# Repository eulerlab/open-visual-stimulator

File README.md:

## Open Visual Stimulator

This repository holds the resources for a flexible, spatial visual stimulator with up to 6 chromatic channels. It combines commercial digital light processing (DLP) devices with open hard- and software components that can be easily adapted to the experimentalist’s specific needs. With this we intend to start a community effort of sharing and further developing a common stimulator design.

Please find more details on the stimulator in the following publication:
  
_Franke K*, Maia Chagas A*, Zhao Z, Zimmermann MJY, Bartel P, Qiu Y, Szatko K, Baden T, Euler T# (2019). An arbitrary-spectrum spatial visual stimulator for vision research. eLife 2019;8:e48779, [10.7554/eLife.48779](https://elifesciences.org/articles/48779)._

For the newest changes and additions, see [release notes](https://github.com/eulerlab/open-visual-stimulator/blob/master/release_notes.md)

### Pictures

_Rendering of the 4-channel R-G-B-UV zebrafish stimulator (by MJY Zimmermann)._

_Rendering of through-the-conderser (TTC) G-UV mouse light stimulator (by MJY Zimmermann)._

_Rendering of through-the-objective (TTO) G-UV mouse light stimulator (by MJY Zimmermann)._ 

### Ordering of PCB boards

If you are interested in ordering boards and components, please find more information in the boards folder [readme](https://github.com/eulerlab/open-visual-stimulator/blob/master/boards/readme.md) file.

## Repository structure

```
├───pics                                      Pictures
├───boards                                    LED driver/blanking boards
│   ├───lcr_add-on                            - KiCad files for board that combines LCr and
|   |   |                                       blanking signals
|   |   ├───connector_coaxial.pretty          - BNC connector description (KiCad)
|   |   └───gerber                            - Gerber files for circuit board
│   ├───mosfet_circuit                        - KiCad files for board that switches switch LEDs
|   |   ├───connector_coaxial.pretty          - BNC connector description (KiCad)
|   |   └───gerber                            - Gerber files for circuit board
|   ├───mosfet_circuit_plus_voltage_regulator - KiCad files for board that combines voltage
|   |   |                                       regulator and LED switching
|   |   ├───connector_coaxial.pretty          - BNC connector description (KiCad)
|   |   └───gerbers                           - Gerber files for circuit board
|   ├───ssr_board                             - KiCad files for solid state relay board
|   |   └───gerbers                           - Gerber files for circuit board
|   └───arduino_code_for_testing_circuits     - Arduino code to emulate blanking and LCr signals
|       └───lcr_emulator
|
├───printed_parts                             OpenSCAD and STL files for 3D printed parts
|   |
│   ├───Fish_cinema                           - Fish tank used in the fish setup
│   ├───SSR_board                             - Designs for plate and cover of the SSR board
│   └───optical_components                    - optomechanical parts for LED assemblies
|           ├───fish_stimulator
|           ├───cmouse_stimulator
|           └───lcr_addons
├───calibration_mouse                         Calibration of dichroic mouse stimulator
│   ├───data                                  - recorded calibration data (custom LEDs and TFT monitor)
│   ├───datasheets                            - spectrometer data sheet, etc.
│   ├───filters                               - dichroic filter spectra
│   ├───light-sources                         - spectra of LEDs
│   ├───opsins                                - mouse opsin sensitivity curves
│   ├───scripts                               - Python scripts used in iPython notebooks
|   └───spectrometer-calibration-files        - USB2+ calibration data
|
└───calibration_zebrafish                     Calibration of tetrachromatic zebrafish stimulator
    ├───data                                  - recorded calibration data (custom LEDs)
    ├───datasheets                            - spectrometer & powermeter data sheet.
    ├───light-sources                         - LED spectra measured behind the teflon screen
    ├───opsins                                - zebrafish opsin sensitivity curves
    └───scripts                               - Python scripts used in iPython notebooks
```

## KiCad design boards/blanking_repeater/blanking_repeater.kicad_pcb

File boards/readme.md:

## LED driver/blanking boards

LED blanking circuits were inspired by earlier devices designed and built by R. Berndt (HIH Tübingen).

`lcr_add-on` - KiCad and Gerber files for the "logic board". This board combines the signals from the LCr with an external "blanking signal" to independently control up to three 3 LEDs per lightcrafter device. This board has a jumper option to disable the blanking signal altogether, which may be useful when e.g. using LCrs in MEA setups.

`mosfet_circuit` - KiCad and Gerber files for "LED driver board". This board uses the 5V logic signal from Lcr_addon ("logic board") to turn LEDs on and off. Users need to connect this board to an appropriate power suply (i.e. a power supply the is outputing the LED forward voltage).

`mosfet_circuit_plus_voltage_regulator` - KiCad and Gerber files for "LED driver board". This board uses the 5V logic signal from Lcr_addon ("logic board") to turn LEDs on and off. This board has a stepdown voltage regulator built-in. It is capable of 20V and 1.5A max output with the components present in its "1-click-bom.csv" file. (see "Components to populate the boards" for more details).

`ssr_board` - This board controls the LED power lines from the Lightcrafter by opening and closing them using solid state relays. The relays are controlled by a 5V signal (in this case the inverted blanking signal).

### General information about the printed circuit boards:

- For details on the design and function of the boards, see [preprint](https://www.biorxiv.org/content/10.1101/649566v1)).

- The boards were designed using [KiCad 5](http://www.kicad.org/) and can be ordered using the `Gerber.zip` file located in each board's `gerber` subfolder.

- Several "board on demand" companies are available, and the process of ordering is pretty much the same. A more detailed tutorial on how to do so can be found [here](https://www.youtube.com/watch?v=ENmDnoKs2hM) (for simply using the already available compressed files, go to minute 7 of the video).

- Companies providing "board on demand" service include:

   - [JLCPCB](https://jlcpcb.com/)
   - [PCBWAY](https://www.pcbway.com)
   - [OSH PARK](https://oshpark.com/)
   - [AISLER](https://aisler.net/)

### Components to populate the boards:

Components are listed on each board folder on a "comma separated value" file named `1-click-bom.csv`. Listed in the file are the quantity, identification and supplier of each component. They can also be ordered using [KitSpace](kitspace.org):

 - [LCr_addon on kitspace](https://kitspace.org/boards/github.com/eulerlab/open-visual-stimulator/boards/lcr_add-on/)
 - [mosfet circuit on kitspace](https://kitspace.org/boards/github.com/eulerlab/open-visual-stimulator/boards/mosfet_circuit/)
 - [mosfet  plus voltage regulator circuit on kitspace](https://kitspace.org/boards/github.com/eulerlab/open-visual-stimulator/boards/mosfet_circuit_plus_voltage_regulator/)

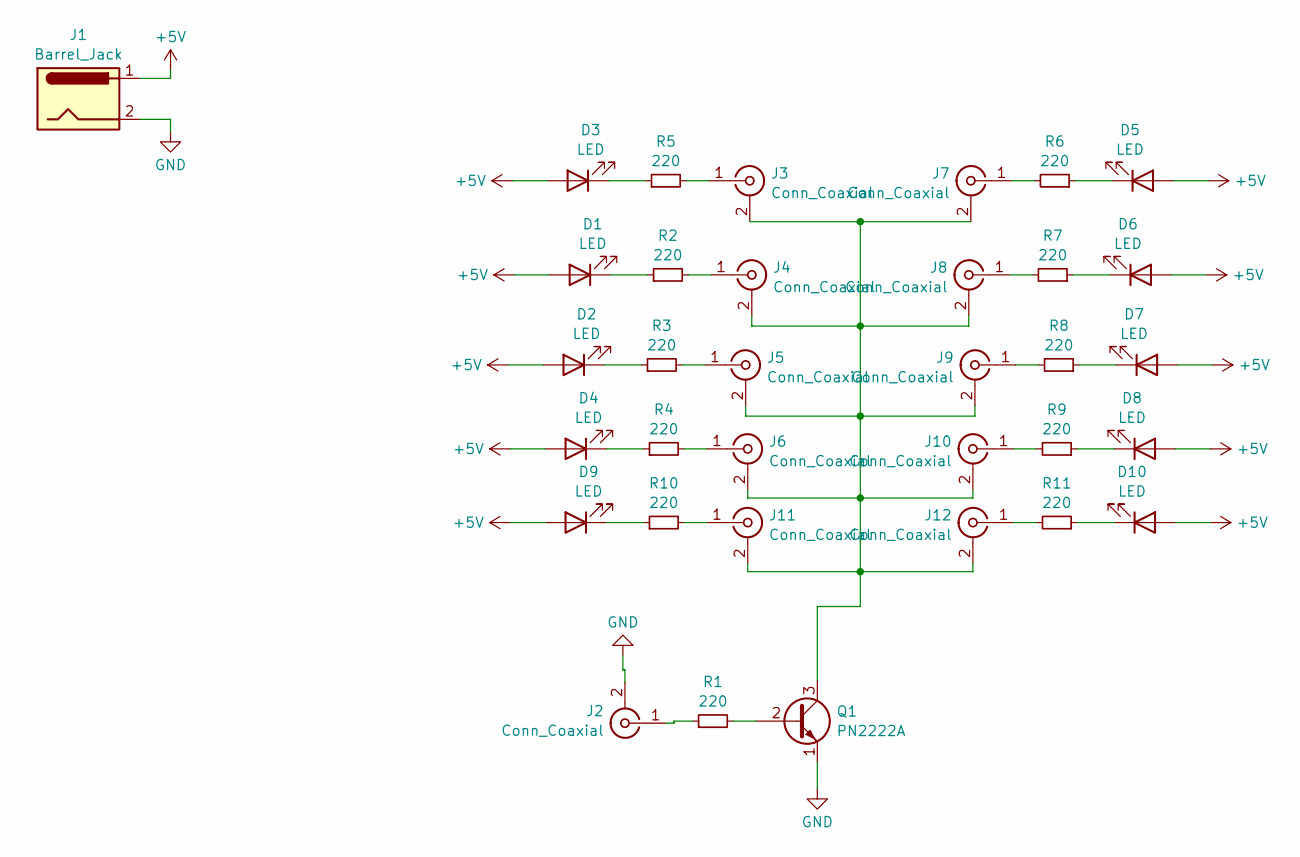
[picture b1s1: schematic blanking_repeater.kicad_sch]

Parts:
D1, D2, D3, D4, D5, D6, D7, D8, D9, D10: LED; LED_D3.0mm_Clear
J1: Barrel_Jack; BarrelJack_Horizontal
J2, J3, J4, J5, J6, J7, J8, J9, J10, J11, J12: Conn_Coaxial; BNC_Amphenol_B6252HB-NPP3G-50_Horizontal
Q1: PN2222A; TO-92_Inline
R1, R2, R3, R4, R5, R6, R7, R8, R9, R10, R11: 220; R_Axial_DIN0207_L6.3mm_D2.5mm_P10.16mm_Horizontal

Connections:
+5V: D1.2 (A), D2.2 (A), D3.2 (A), D4.2 (A), D5.2 (A), D6.2 (A), D7.2 (A), D8.2 (A), D9.2 (A), D10.2 (A), J1.1
GND: J1.2, J2.2 (Ext), Q1.1 (E)
unnamed: D1.1 (K), R2.1
unnamed: D2.1 (K), R3.1
unnamed: D3.1 (K), R5.1
unnamed: D4.1 (K), R4.1
unnamed: D5.1 (K), R6.1
unnamed: D6.1 (K), R7.1
unnamed: D7.1 (K), R8.1
unnamed: D8.1 (K), R9.1
unnamed: D9.1 (K), R10.1
unnamed: D10.1 (K), R11.1
unnamed: J2.1 (In), R1.1
unnamed: J3.1 (In), R5.2
unnamed: J4.1 (In), R2.2
unnamed: J5.1 (In), R3.2
unnamed: J6.1 (In), R4.2
unnamed: J7.1 (In), R6.2
unnamed: J8.1 (In), R7.2
unnamed: J9.1 (In), R8.2
unnamed: J3.2 (Ext), J4.2 (Ext), J5.2 (Ext), J6.2 (Ext), J7.2 (Ext), J8.2 (Ext), J9.2 (Ext), J10.2 (Ext), J11.2 (Ext), J12.2 (Ext), Q1.3 (C)
unnamed: J10.1 (In), R9.2
unnamed: J11.1 (In), R10.2
unnamed: J12.1 (In), R11.2
unnamed: Q1.2 (B), R1.2

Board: 2 copper layers, 34 parts (0 on the bottom side), 25 nets, no tracks yet.

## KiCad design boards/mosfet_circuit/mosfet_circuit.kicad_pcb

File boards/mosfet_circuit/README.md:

# Open Visual Stimulator - MOSFET Circuit PCB

A board ("LED driver board") for fast switching LEDs on/off, part of the Open Source visual stimulator project.

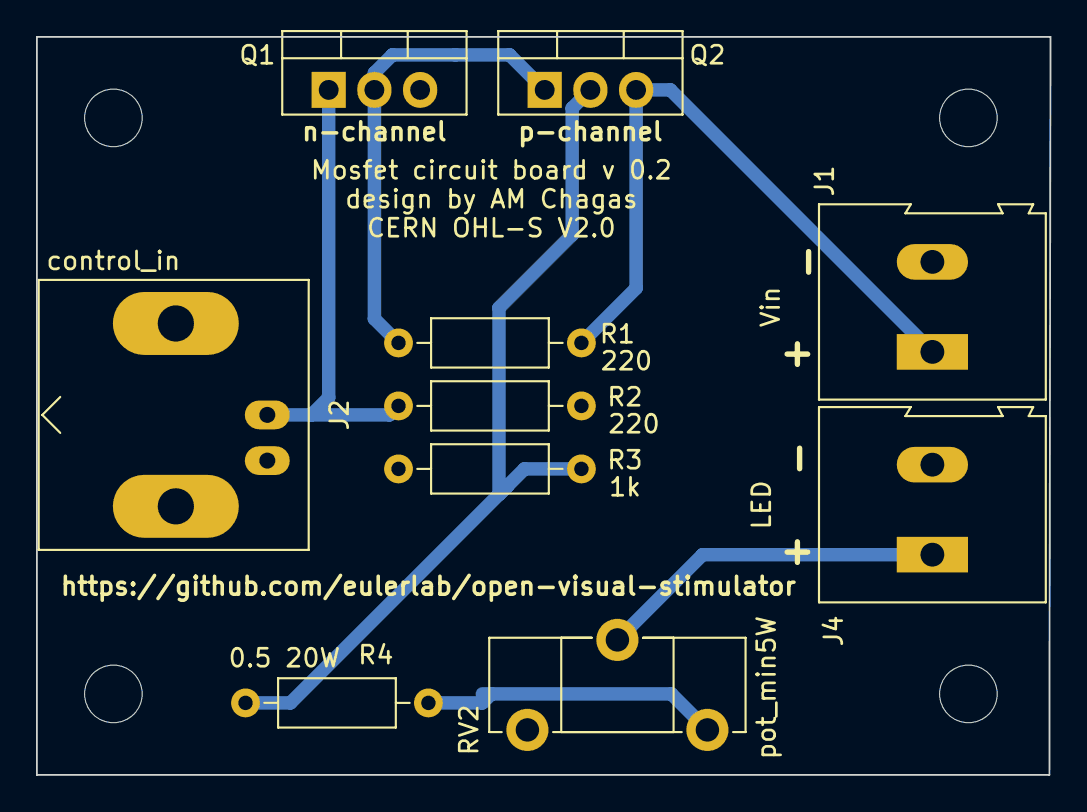
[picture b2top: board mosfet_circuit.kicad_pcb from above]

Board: 2 copper layers, 56.3 x 41.0 mm, 14 parts (0 on the bottom side), 7 nets.

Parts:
H1, H2, H3, H4: MountingHole; MountingHole_3.2mm_M3_DIN965
J1: Vin; TerminalBlock_Altech_AK300-2_P5.00mm
J2: control_in; BNC_Amphenol_B6252HB-NPP3G-50_Horizontal
J4: LED; TerminalBlock_Altech_AK300-2_P5.00mm
Q1: BUZ11; TO-220-3_Vertical
Q2: IRF4905; TO-220-3_Vertical
R1, R2: 220; R_Axial_DIN0207_L6.3mm_D2.5mm_P10.16mm_Horizontal
R3: 1k; R_Axial_DIN0207_L6.3mm_D2.5mm_P10.16mm_Horizontal
R4: 0.5 20W; R_Axial_DIN0207_L6.3mm_D2.5mm_P10.16mm_Horizontal
RV2: pot_min5W; Potentiometer_ACP_CA14-H5_Horizontal

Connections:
GND: J1.2, J2.2 (Ext), J4.2, Q1.3 (S), R2.1, R3.2
unnamed: J1.1, Q2.3 (S), R1.2
unnamed: J2.1 (In), Q1.1 (G), R2.2
unnamed: J4.1, RV2.2
unnamed: Q1.2 (D), Q2.1 (G), R1.1
unnamed: Q2.2 (D), R3.1, R4.2
unnamed: R4.1, RV2.3

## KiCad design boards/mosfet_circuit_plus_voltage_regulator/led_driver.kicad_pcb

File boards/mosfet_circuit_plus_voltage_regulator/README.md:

# Open Visual Stimulator - mosfet circuit plus voltage regulator

A board that contains a voltage regulator and a fast switching (tens of microsseconds) circuit for turning LEDs on and off

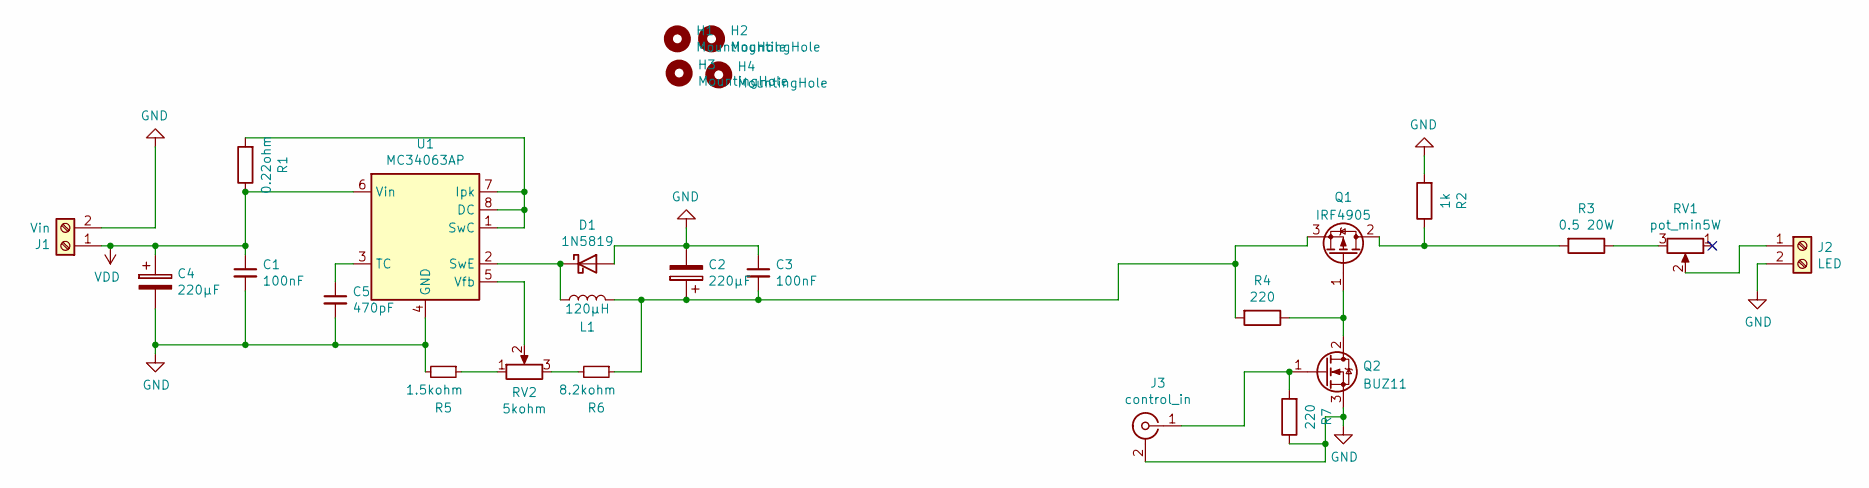
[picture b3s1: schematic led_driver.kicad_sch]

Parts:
C1, C3: 100nF; C_Disc_D8.0mm_W5.0mm_P7.50mm
C2, C4: 220µF; CP_Radial_D8.0mm_P5.00mm
C5: 470pF; C_Axial_L5.1mm_D3.1mm_P7.50mm_Horizontal
D1: 1N5819; D_DO-41_SOD81_P10.16mm_Horizontal
H1, H2, H3, H4: MountingHole; MountingHole_3.2mm_M3
J1: Vin; TerminalBlock_Altech_AK300-2_P5.00mm
J2: LED; TerminalBlock_Altech_AK300-2_P5.00mm
J3: control_in; BNC_Amphenol_B6252HB-NPP3G-50_Horizontal
L1: 120µH; L_Radial_D7.5mm_P5.00mm_Fastron_07P
Q1: IRF4905; TO-220-3_Vertical
Q2: BUZ11; TO-220-3_Vertical
R1: 0.22ohm; R_Axial_DIN0414_L11.9mm_D4.5mm_P15.24mm_Horizontal
R2: 1k; R_Axial_DIN0207_L6.3mm_D2.5mm_P10.16mm_Horizontal
R3: 0.5 20W; TO-220-2_Vertical
R4, R7: 220; R_Axial_DIN0207_L6.3mm_D2.5mm_P10.16mm_Horizontal
R5: 1.5kohm; R_Axial_DIN0207_L6.3mm_D2.5mm_P10.16mm_Horizontal
R6: 8.2kohm; R_Axial_DIN0207_L6.3mm_D2.5mm_P10.16mm_Horizontal
RV1: pot_min5W; Potentiometer_ACP_CA14-H5_Horizontal
RV2: 5kohm; Potentiometer_Vishay_T73YP_Vertical
U1: MC34063AP; DIP-8_W7.62mm

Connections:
GND: C1.2, C2.2, C3.1, C4.2, C5.2, D1.2 (A), J1.2, J2.2, J3.2 (Ext), Q2.3 (S), R2.2, R5.2, R7.1, U1.4 (GND)
unnamed: C2.1, C3.2, L1.2, Q1.3 (S), R4.2, R6.1
unnamed: C5.1, U1.3 (TC)
unnamed: D1.1 (K), L1.1, U1.2 (SwE)
unnamed: J2.1, RV1.2
unnamed: J3.1 (In), Q2.1 (G), R7.2
unnamed: Q1.1 (G), Q2.2 (D), R4.1
unnamed: Q1.2 (D), R2.1, R3.2
unnamed: R1.2, U1.1 (SwC), U1.7 (Ipk), U1.8 (DC)
unnamed: R3.1, RV1.3
unnamed: R5.1, RV2.1
unnamed: R6.2, RV2.3
unnamed: RV2.2, U1.5 (Vfb)
VDD: C1.1, C4.1, J1.1, R1.1, U1.6 (Vin)

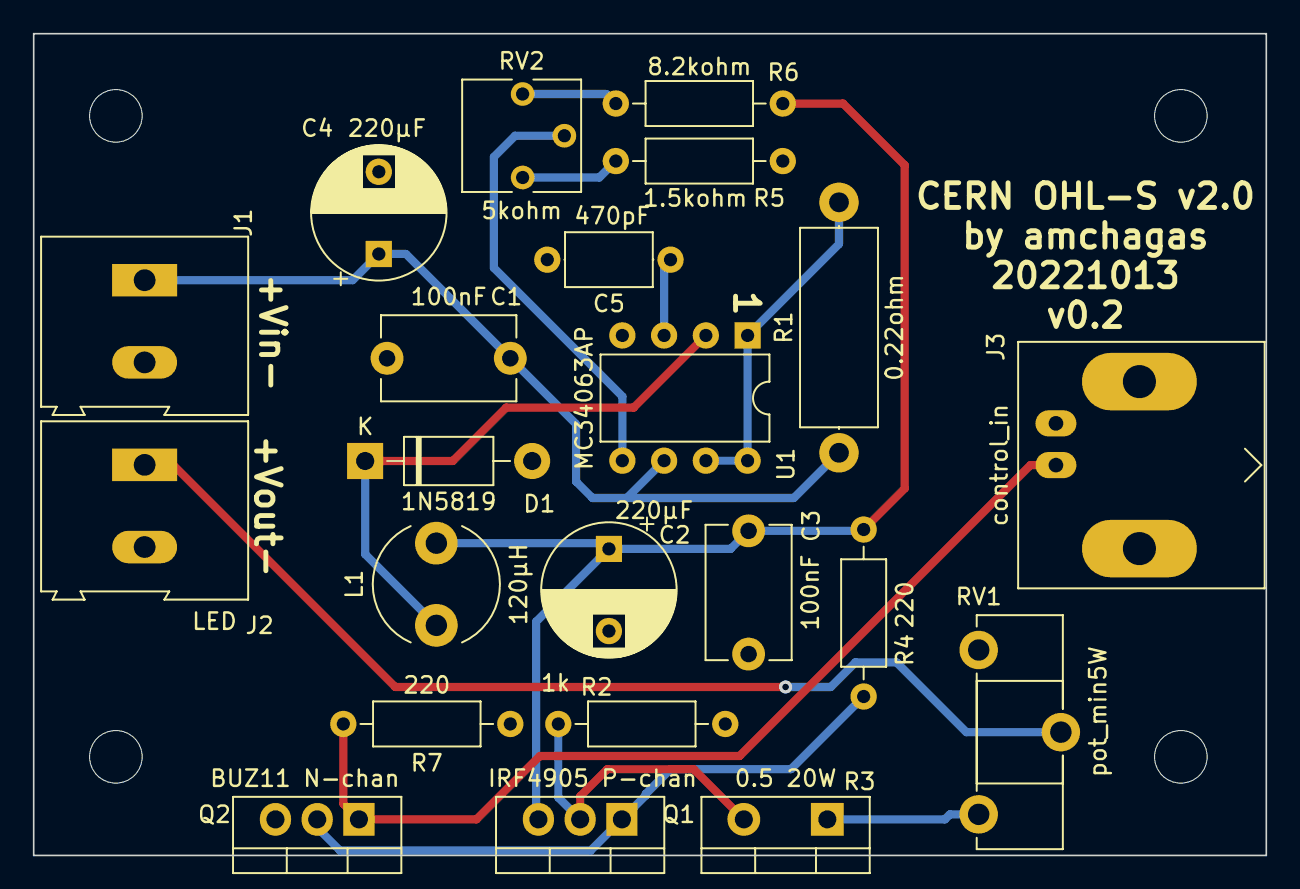
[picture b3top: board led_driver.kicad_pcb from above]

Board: 2 copper layers, 75.0 x 50.0 mm, 26 parts (0 on the bottom side), 14 nets.

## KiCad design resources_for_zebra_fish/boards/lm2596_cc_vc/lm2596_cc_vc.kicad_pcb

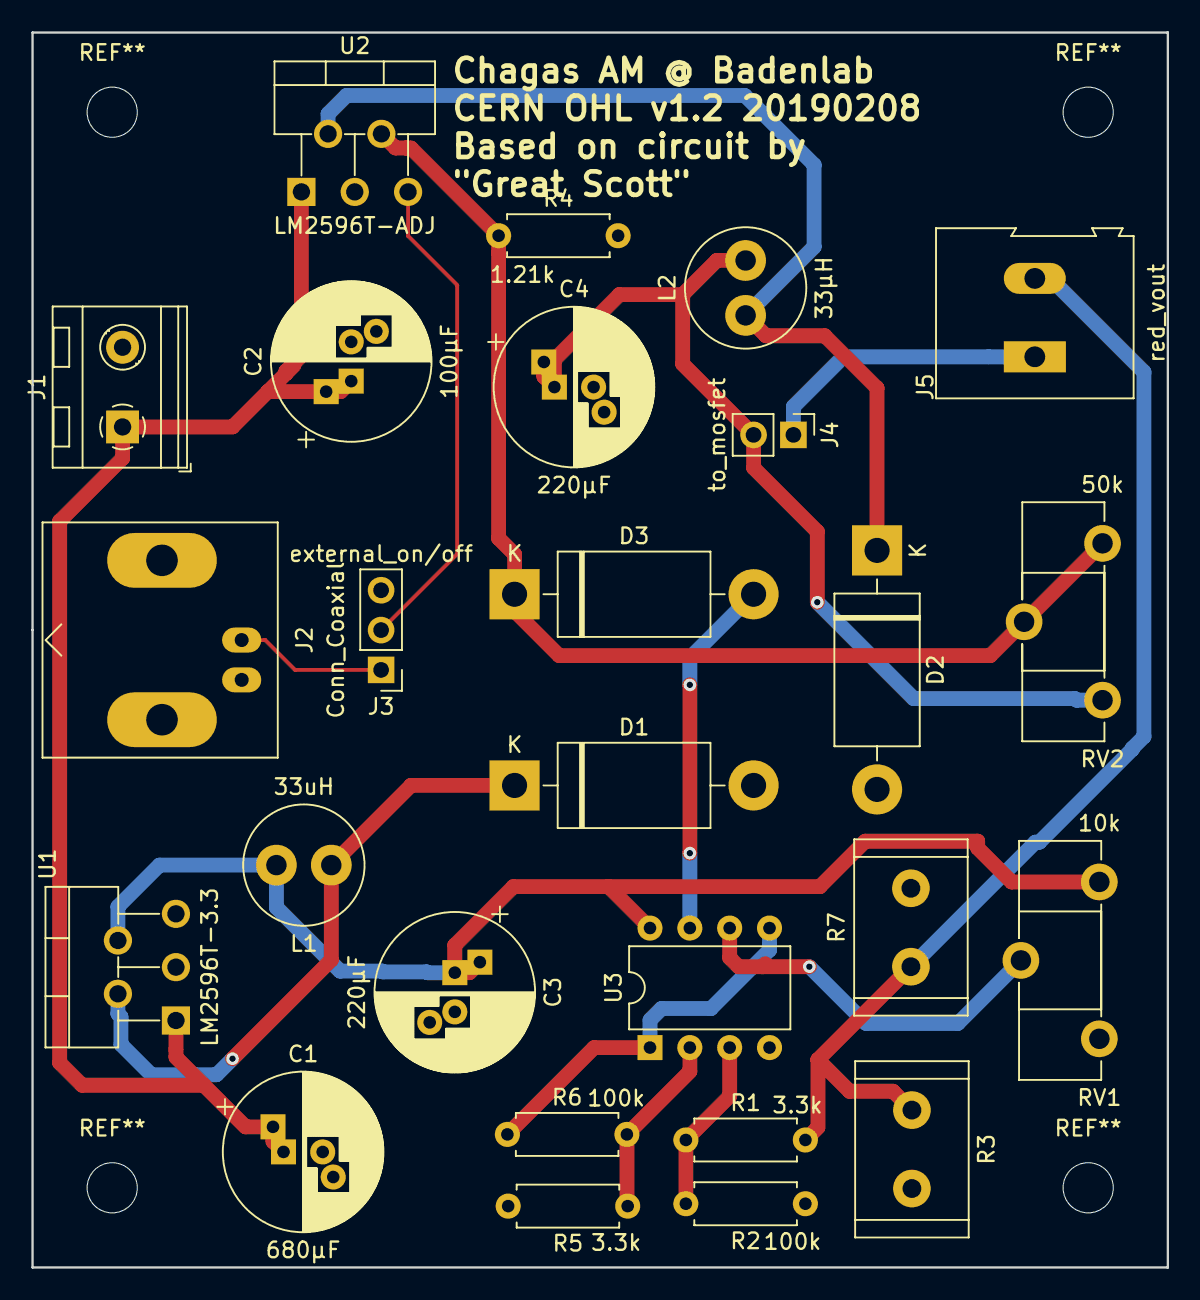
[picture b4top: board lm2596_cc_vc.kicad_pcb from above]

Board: 2 copper layers, 72.4 x 78.7 mm, 26 parts (0 on the bottom side), 16 nets.

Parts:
C1: 680µF; CP_Radial_D10.0mm_P2.50mm_P5.00mm
C2: 100µF; CP_Radial_D10.0mm_P2.50mm_P5.00mm
C3, C4: 220µF; CP_Radial_D10.0mm_P2.50mm_P5.00mm
D1, D2, D3: 1N5822; D_DO-201AD_P15.24mm_Horizontal
J1: Vin; TerminalBlock_RND_205-00232_1x02_P5.08mm_Horizontal
J2: Conn_Coaxial; BNC_Amphenol_B6252HB-NPP3G-50_Horizontal
J3: external_on/off; PinHeader_1x03_P2.54mm_Vertical
J4: to_mosfet; PinHeader_1x02_P2.54mm_Vertical
J5: red_vout; TerminalBlock_Altech_AK300-2_P5.00mm
L1: 33uH; L_Radial_D7.5mm_P3.50mm_Fastron_07P
L2: 33µH; L_Radial_D7.5mm_P3.50mm_Fastron_07P
R1, R5: 3.3k; R_Axial_DIN0207_L6.3mm_D2.5mm_P7.62mm_Horizontal
R2, R6: 100k; R_Axial_DIN0207_L6.3mm_D2.5mm_P7.62mm_Horizontal
R3, R7: 0.1; R_Radial_Power_L11.0mm_W7.0mm_P5.00mm
R4: 1.21k; R_Axial_DIN0207_L6.3mm_D2.5mm_P7.62mm_Horizontal
RV1: 10k; Potentiometer_Piher_PT-15-H25_Horizontal
RV2: 50k; Potentiometer_Piher_PT-15-H25_Horizontal
U1: LM2596T-3.3; TO-220-5_P3.4x3.7mm_StaggerOdd_Lead3.8mm_Vertical
U2: LM2596T-ADJ; TO-220-5_P3.4x3.7mm_StaggerOdd_Lead3.8mm_Vertical
U3: MCP602; DIP-8_W7.62mm

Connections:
+3V3: C3.1, L1.2, RV1.3, U1.4, U3.8
+24V: C1.1, C2.1, J1.1, U1.1, U2.1
GND: C1.2, C2.2, C3.2, C4.2, D1.2, D2.2, J1.2, J2.2, J3.3, R2.1, R3.2, R4.2, R5.2, R7.2, RV1.1, U1.3, U1.5, U2.3, U3.4
unnamed: C4.1, J4.2, L2.2, RV2.1
unnamed: D1.1, L1.1, U1.2
unnamed: D2.1, L2.1, U2.2
unnamed: D3.1, R4.1, RV2.2, RV2.3, U2.4
unnamed: D3.2, U3.7
unnamed: J2.1, J3.1
unnamed: J3.2, U2.5
unnamed: J4.1, J5.1
unnamed: J5.2, R1.2, R3.1, R7.1
unnamed: R1.1, R2.2, U3.3
unnamed: R5.1, R6.2, U3.2
unnamed: R6.1, U3.1, U3.5
unnamed: RV1.2, U3.6

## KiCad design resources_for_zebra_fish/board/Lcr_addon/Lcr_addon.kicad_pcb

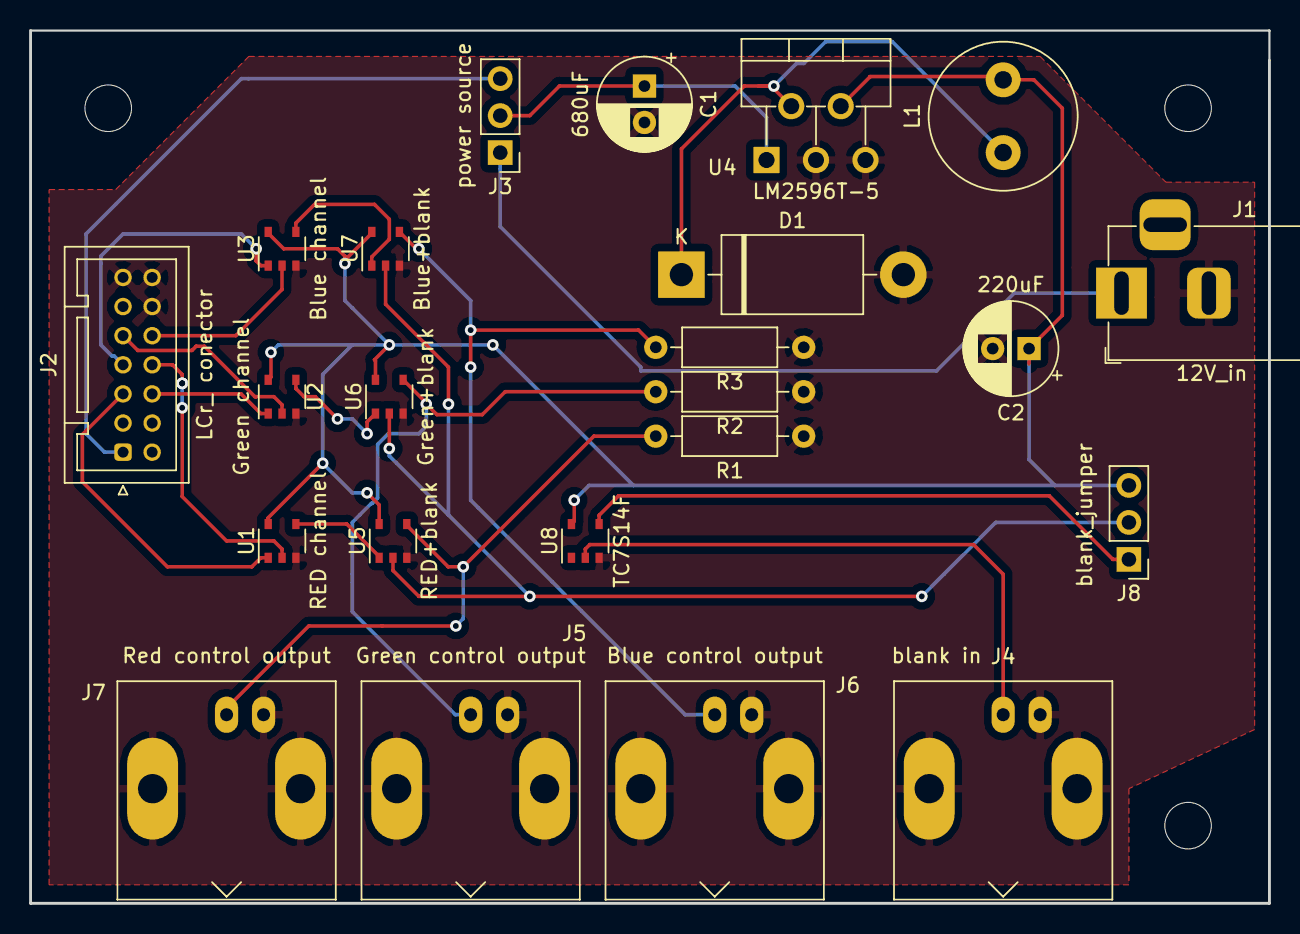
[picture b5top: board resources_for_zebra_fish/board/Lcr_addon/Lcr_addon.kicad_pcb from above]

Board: 2 copper layers, 85.1 x 59.9 mm, 23 parts (0 on the bottom side), 21 nets.

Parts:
C1: 680uF; CP_Radial_D6.3mm_P2.50mm
C2: 220uF; CP_Radial_D6.3mm_P2.50mm
D1: D_Schottky; D_DO-201AD_P15.24mm_Horizontal
J1: 12V_in; BarrelJack_Horizontal
J2: LCr_ conector; JST_PUD_B14B-PUDSS_2x07_P2.00mm_Vertical
J3: power source; PinHeader_1x03_P2.54mm_Vertical
J4: blank in; BNC_Amphenol_B6252HB-NPP3G-50_Horizontal
J5: Green control output; BNC_Amphenol_B6252HB-NPP3G-50_Horizontal
J6: Blue control output; BNC_Amphenol_B6252HB-NPP3G-50_Horizontal
J7: Red control output; BNC_Amphenol_B6252HB-NPP3G-50_Horizontal
J8: blank_jumper; PinHeader_1x03_P2.54mm_Vertical
L1: 33uH; L_Radial_D10.0mm_P5.00mm_Neosid_SD12_style3
R1, R2, R3: 1k; R_Axial_DIN0207_L6.3mm_D2.5mm_P10.16mm_Horizontal
U1: RED channel; TSOP-5_1.65x3.05mm_P0.95mm
U2: Green channel; TSOP-5_1.65x3.05mm_P0.95mm
U3: Blue channel; TSOP-5_1.65x3.05mm_P0.95mm
U4: LM2596T-5; TO-220-5_P3.4x3.7mm_StaggerOdd_Lead3.8mm_Vertical
U5: RED+blank; TSOP-5_1.65x3.05mm_P0.95mm
U6: Green+blank; TSOP-5_1.65x3.05mm_P0.95mm
U7: Blue+blank; TSOP-5_1.65x3.05mm_P0.95mm
U8: TC7S14F; TSOP-5_1.65x3.05mm_P0.95mm

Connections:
+12V: J1.1, J3.1
GND: C1.2, C2.2, D1.2, J1.2, J2.12, J2.13, J2.14, J4.2, J5.2, J6.2, J7.2, R1.1, R2.1, R3.1, U1.3, U2.3, U3.3, U4.3, U4.5, U5.3, U6.3, U7.3, U8.3
unnamed: C1.1, J3.2, U4.1
unnamed: D1.1, L1.1, U4.2
unnamed: J2.1, J3.3
unnamed: J2.5, U1.1
unnamed: J2.6, U2.1
unnamed: J2.7, U3.1
unnamed: J2.8, U1.2
unnamed: J2.9, U2.2
unnamed: J2.10, U3.2
unnamed: J4.1, U8.2
unnamed: J5.1, R2.2, U6.4
unnamed: J6.1, R3.2, U7.4
unnamed: J7.1, R1.2, U5.4
unnamed: J8.1, U8.4
unnamed: J8.2, U5.2, U6.2, U7.2
unnamed: U1.4, U5.1
unnamed: U2.4, U6.1
unnamed: U3.4, U7.1
VCC: C2.1, J8.3, L1.2, U1.5, U2.5, U3.5, U4.4, U5.5, U6.5, U7.5, U8.5

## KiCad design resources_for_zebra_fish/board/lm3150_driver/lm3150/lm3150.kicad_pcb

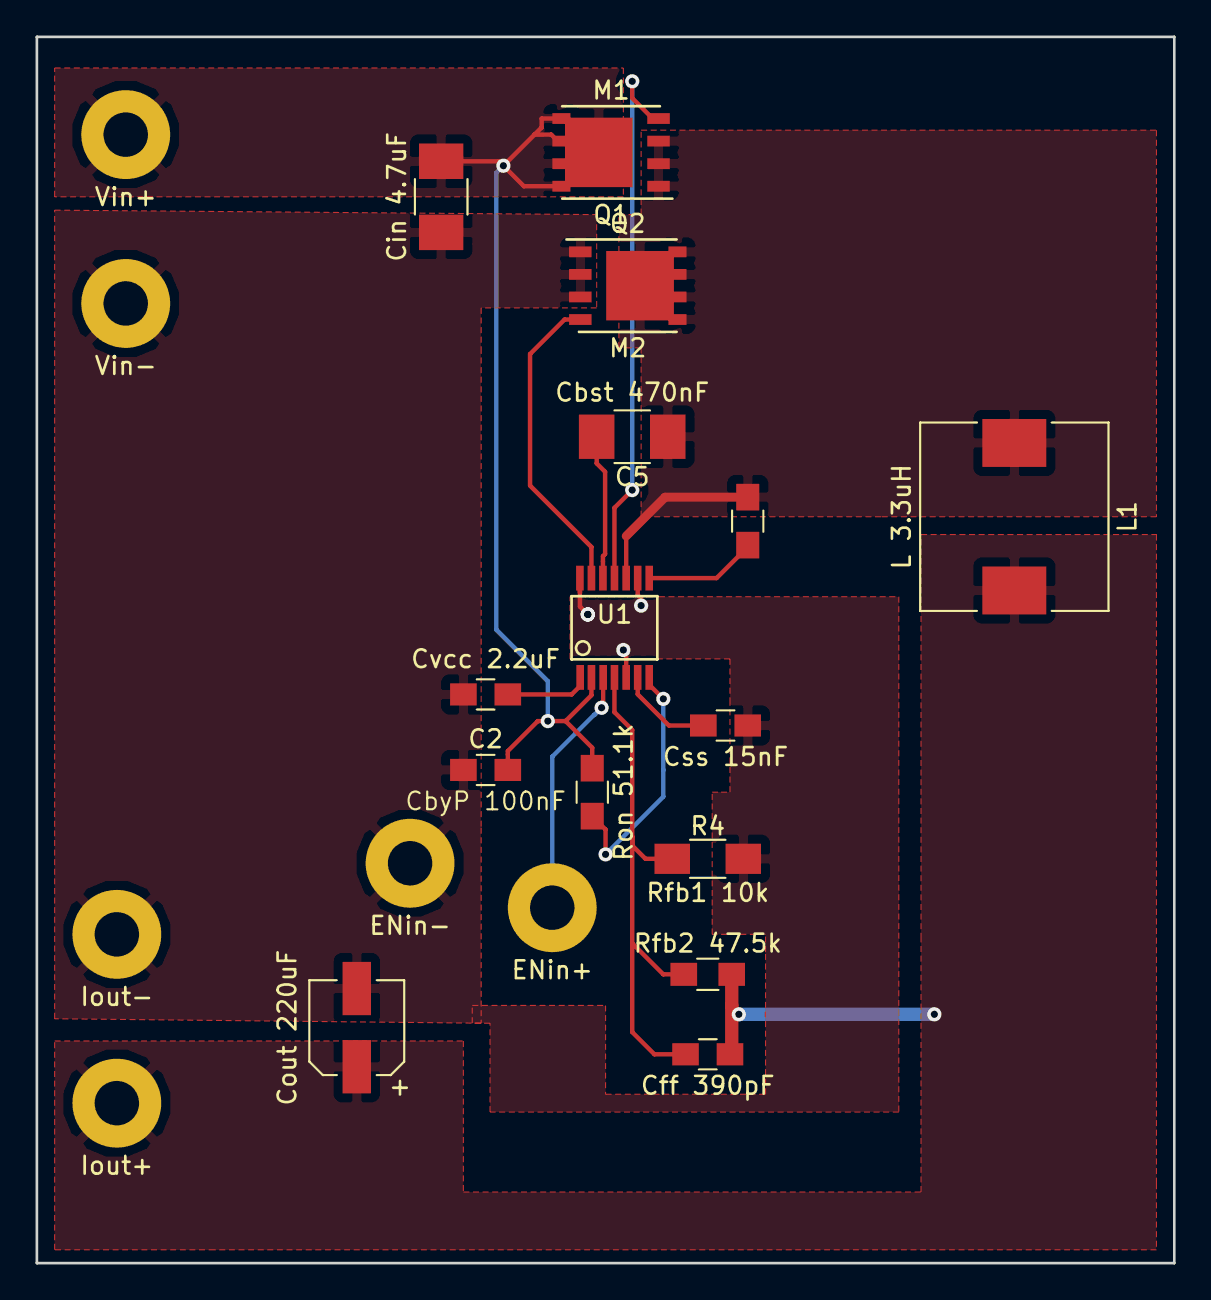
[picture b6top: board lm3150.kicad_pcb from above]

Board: 2 copper layers, 64.0 x 69.0 mm, 21 parts (0 on the bottom side), 13 nets.

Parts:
C1: Cin 4.7uF; C_1210_HandSoldering
C2: CbyP 100nF; C_0805_HandSoldering
C3: Css 15nF; C_0805_HandSoldering
C4: Cvcc 2.2uF; C_0805_HandSoldering
C5: Cbst 470nF; C_1210_HandSoldering
C6: Cff 390pF; C_0805_HandSoldering
C7: Cout 220uF; CP_Elec_5x5.8
L1: L 3.3uH; L_10.4x10.4_H4.8
MH1: Vin-; MountingHole_2.5mm_Pad
MH2: Vin+; MountingHole_2.5mm_Pad
MH3: ENin-; MountingHole_2.5mm_Pad
MH4: ENin+; MountingHole_2.5mm_Pad
MH5: Iout+; MountingHole_2.5mm_Pad
MH6: Iout-; MountingHole_2.5mm_Pad
Q1: M1; SO-8_PowerPAK_Vishay_Single
Q2: M2; SO-8_PowerPAK_Vishay_Single
R1: Ron 51.1k; R_0805_HandSoldering
R2: Rilim 475; R_0805_HandSoldering
R3: Rfb2 47.5k; R_0805_HandSoldering
R4: Rfb1 10k; R_1206_HandSoldering
U1: LM3150; SSOP-14

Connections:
+12V: C1.1, C2.2, MH2.1, Q1.5, R1.1, U1.2
GND: C1.2, C2.1, C3.2, C4.1, C7.2, MH1.1, MH3.1, MH6.1, Q2.1, Q2.2, Q2.3, R4.2, U1.5, U1.9, U1.14
unnamed: C3.1, U1.6
unnamed: C4.2, U1.1
unnamed: C5.1, L1.1, Q1.1, Q1.2, Q1.3, Q2.5, R2.2, U1.10
unnamed: C5.2, U1.12
unnamed: C6.1, R3.2, R4.1, U1.4
unnamed: C6.2, C7.1, L1.2, MH5.1, R3.1
unnamed: MH4.1, U1.3
unnamed: Q1.4, U1.11
unnamed: Q2.4, U1.13
unnamed: R1.2, U1.7
unnamed: R2.1, U1.8

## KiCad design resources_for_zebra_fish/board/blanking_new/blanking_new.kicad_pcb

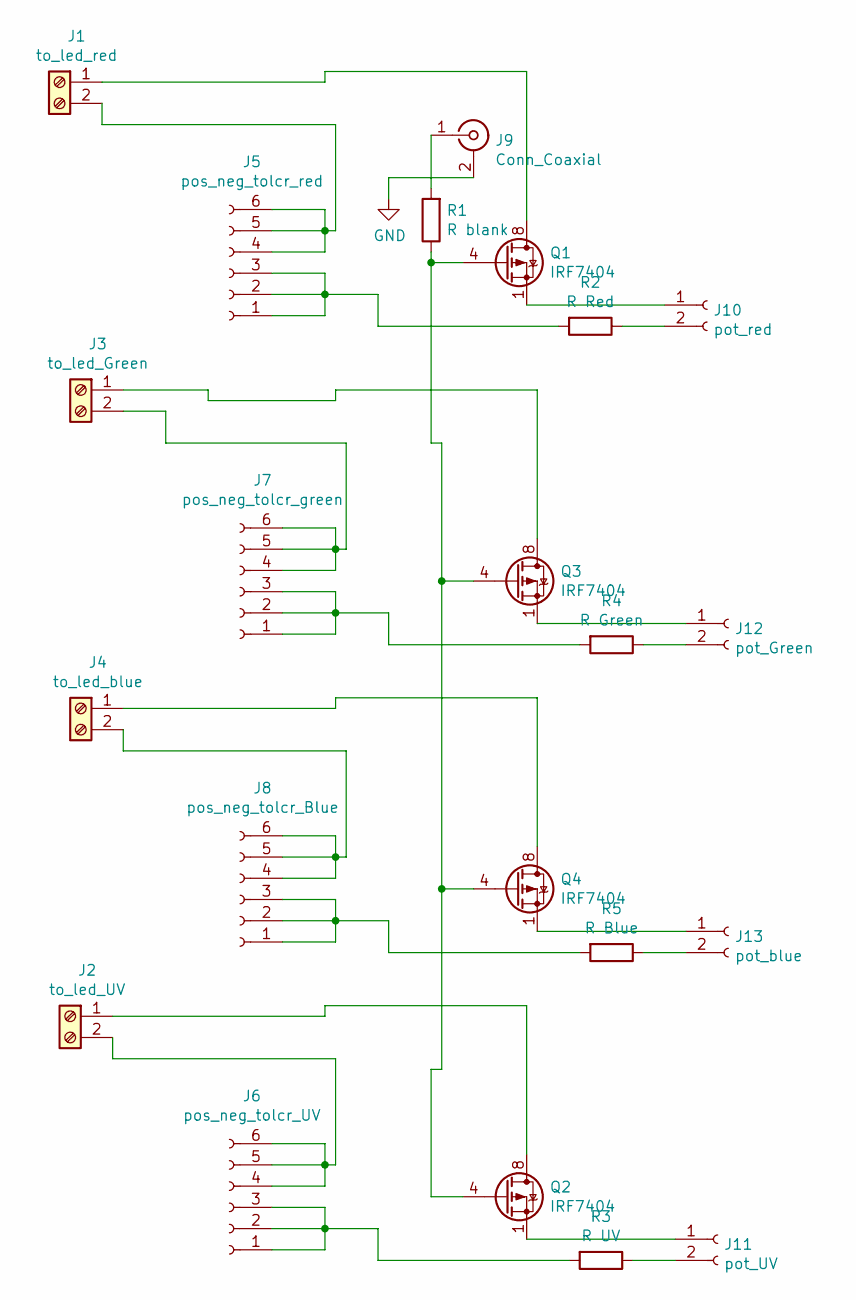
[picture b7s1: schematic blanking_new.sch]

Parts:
J1: to_led_red; PinHeader_1x02_P2.54mm_Vertical
J2: to_led_UV; PinHeader_1x02_P2.54mm_Vertical
J3: to_led_Green; PinHeader_1x02_P2.54mm_Vertical
J4: to_led_blue; PinHeader_1x02_P2.54mm_Vertical
J5: pos_neg_tolcr_red; Molex_SPOX_5267-06A_1x06_P2.50mm_Vertical
J6: pos_neg_tolcr_UV; Molex_SPOX_5267-06A_1x06_P2.50mm_Vertical
J7: pos_neg_tolcr_green; Molex_SPOX_5267-06A_1x06_P2.50mm_Vertical
J8: pos_neg_tolcr_Blue; Molex_SPOX_5267-06A_1x06_P2.50mm_Vertical
J9: Conn_Coaxial; SMB_Jack_Vertical
J10: pot_red; PinHeader_1x02_P2.54mm_Vertical
J11: pot_UV; PinHeader_1x02_P2.54mm_Vertical
J12: pot_Green; PinHeader_1x02_P2.54mm_Vertical
J13: pot_blue; PinHeader_1x02_P2.54mm_Vertical
Q1, Q2, Q3, Q4: IRF7404; SOIC-8_3.9x4.9mm_P1.27mm
R1: R blank; R_Axial_DIN0309_L9.0mm_D3.2mm_P12.70mm_Horizontal
R2: R Red; R_Axial_Power_L75.0mm_W9.0mm_P86.36mm
R3: R UV; R_Axial_Power_L75.0mm_W9.0mm_P86.36mm
R4: R Green; R_Axial_Power_L75.0mm_W9.0mm_P86.36mm
R5: R Blue; R_Axial_Power_L75.0mm_W9.0mm_P86.36mm

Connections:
GND: J9.2 (Ext)
unnamed: J1.1, Q1.5 (D), Q1.6 (D), Q1.7 (D), Q1.8 (D)
unnamed: J1.2, J5.4, J5.5, J5.6
unnamed: J2.1, Q2.5 (D), Q2.6 (D), Q2.7 (D), Q2.8 (D)
unnamed: J2.2, J6.4, J6.5, J6.6
unnamed: J3.1, Q3.5 (D), Q3.6 (D), Q3.7 (D), Q3.8 (D)
unnamed: J3.2, J7.4, J7.5, J7.6
unnamed: J4.1, Q4.5 (D), Q4.6 (D), Q4.7 (D), Q4.8 (D)
unnamed: J4.2, J8.4, J8.5, J8.6
unnamed: J5.1, J5.2, J5.3, R2.2
unnamed: J6.1, J6.2, J6.3, R3.2
unnamed: J7.1, J7.2, J7.3, R4.2
unnamed: J8.1, J8.2, J8.3, R5.2
unnamed: J9.1 (In), R1.2
unnamed: J10.1, Q1.1 (S), Q1.2 (S), Q1.3 (S)
unnamed: J10.2, R2.1
unnamed: J11.1, Q2.1 (S), Q2.2 (S), Q2.3 (S)
unnamed: J11.2, R3.1
unnamed: J12.1, Q3.1 (S), Q3.2 (S), Q3.3 (S)
unnamed: J12.2, R4.1
unnamed: J13.1, Q4.1 (S), Q4.2 (S), Q4.3 (S)
unnamed: J13.2, R5.1
unnamed: Q1.4 (G), Q2.4 (G), Q3.4 (G), Q4.4 (G), R1.1

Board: 2 copper layers, 22 parts (0 on the bottom side), 22 nets, no tracks yet.

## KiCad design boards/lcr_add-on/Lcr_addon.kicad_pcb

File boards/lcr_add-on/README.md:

# Open Visual Stimulator - LCR add-on PCB

A board for integrating signals from a lightcrafter to a 2P microscope ("logic board"), part of the Open source visual stimulator project.

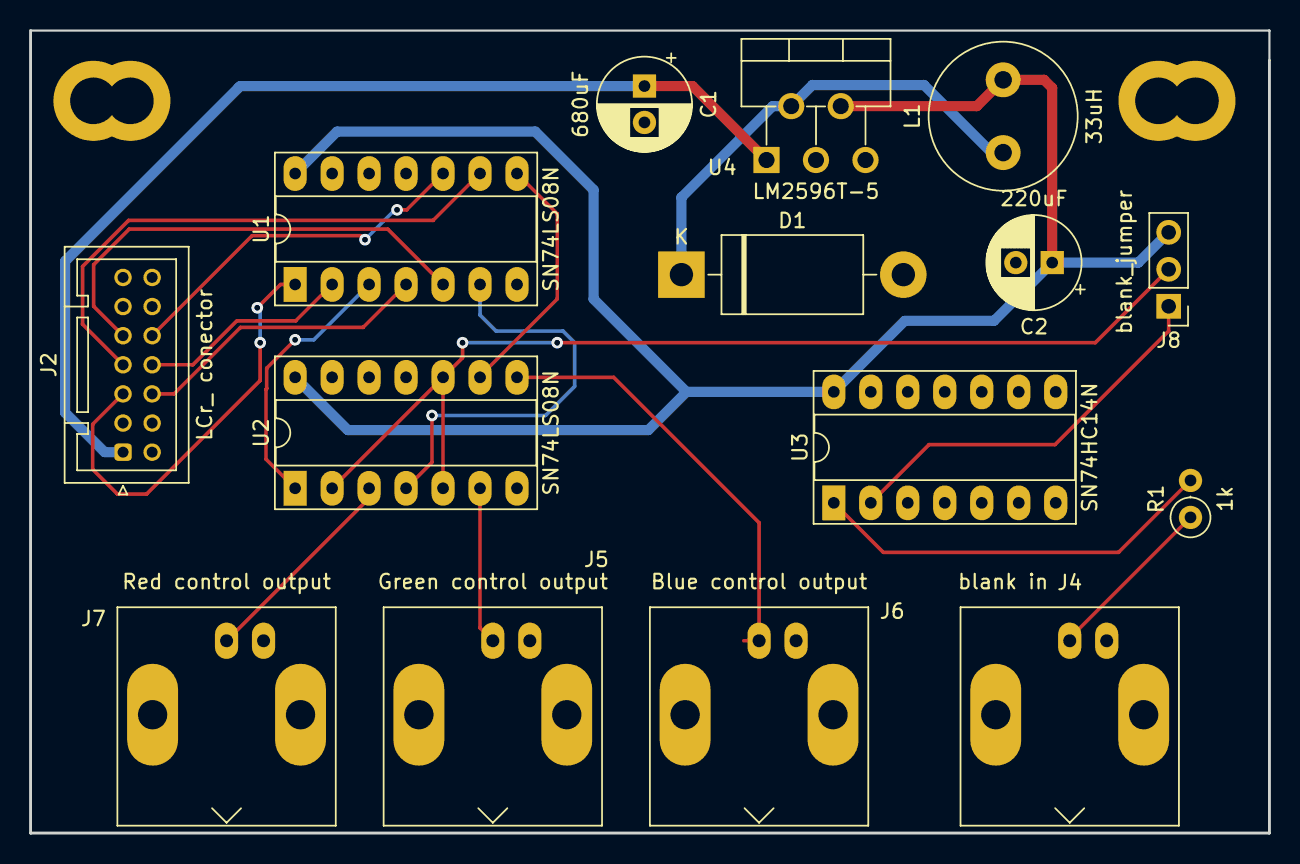
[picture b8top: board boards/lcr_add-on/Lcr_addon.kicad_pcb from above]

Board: 2 copper layers, 85.1 x 55.1 mm, 15 parts (0 on the bottom side), 20 nets.

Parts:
C1: 680uF; CP_Radial_D6.3mm_P2.50mm
C2: 220uF; CP_Radial_D6.3mm_P2.50mm
D1: D_Schottky; D_DO-201AD_P15.24mm_Horizontal
J2: LCr_ conector; JST_PUD_B14B-PUDSS_2x07_P2.00mm_Vertical
J4: blank in; BNC_Amphenol_B6252HB-NPP3G-50_Horizontal
J5: Green control output; BNC_Amphenol_B6252HB-NPP3G-50_Horizontal
J6: Blue control output; BNC_Amphenol_B6252HB-NPP3G-50_Horizontal
J7: Red control output; BNC_Amphenol_B6252HB-NPP3G-50_Horizontal
J8: blank_jumper; PinHeader_1x03_P2.54mm_Vertical
L1: 33uH; L_Radial_D10.0mm_P5.00mm_Neosid_SD12_style3
R1: 1k; R_Axial_DIN0207_L6.3mm_D2.5mm_P2.54mm_Vertical
U1, U2: SN74LS08N; DIP-14_W7.62mm_Socket_LongPads
U3: SN74HC14N; DIP-14_W7.62mm_Socket_LongPads
U4: LM2596T-5; TO-220-5_P3.4x3.7mm_StaggerOdd_Lead3.8mm_Vertical

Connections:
+5V: C2.1, J8.3, L1.2, U1.14, U2.14, U3.14, U4.4
+12V: C1.1, J2.1, U4.1
GND: C1.2, C2.2, D1.2, J2.12, J2.13, J2.14, J4.2, J5.2, J6.2, J7.2, U1.7, U2.7, U3.7, U4.3, U4.5
unnamed: D1.1, L1.1, U4.2
unnamed: J4.1, R1.1
unnamed: J5.1, U2.6
unnamed: J6.1, U2.8
unnamed: J7.1, U2.3
unnamed: R1.2, U3.1
unnamed: U1.3, U2.1
unnamed: U1.6, U2.4
unnamed: U1.8, U2.9
blue_sig1: J2.7, U1.9
blue_sig2: J2.10, U1.10
green_sig1: J2.6, U1.4
green_sig2: J2.9, U1.5
inv_blank-or-5V-input: J8.2, U2.2, U2.5, U2.10
inverted_blank: J8.1, U3.2
red_sig1: J2.5, U1.1
red_sig2: J2.8, U1.2

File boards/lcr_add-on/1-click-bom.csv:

References,Qty,Description,Manufacturer,MPN,Manufacturer_1,MPN_2,Manufacturer_3,MPN_4,Manufacturer_5,MPN_6,Manufacturer_7,MPN_8,Digikey,Mouser,RS,Newark,Farnell
U4;,1,LM2596 5v,ITO-220,Texas Instruments,Texas Instruments,LM2596T-5.0/NOPB,,,,,,,LM2596T-5.0/NOPB-ND,926LM2596T5.0/NOPB,5333743,97K3256,1150103
L1;,1,INDUCTOR 33µH Neosid MA-Bs75,Bourns,RLB0914-330KL,,,,,,,,,RLB0914-330KL-ND,652RLB0914330KL,8118853,61J7916,2309242
D1;,1,Diode Schottky 5A DO-201AD,Vishay,1N5822-E3/73,Zetex,SB5100-T,,,,,,,1N5822-E3/73GICT-ND,6251N5822E3/73,751-4843,17T8202,1336553
C2;,1,CAP ALUM 220UF 20% 25V RADIAL,Panasonic, EEU-FM1E221 ,Panasonic,ECA-1CM221B,Panasonic,ECE-A0GKS221,Panasonic,EEU-EB1A221S,,,P12383-ND,667ECA1CM221B,7472036,70K9673,9451099
C1;,1,680µF Capacitor,Rubycon,16ZL680MEFC10X16,Panasonic,EEU-FC1A681,,,,,,,1189-3978-ND,667EEUFC1A681,7037258,31M6417,1144691
R1;,1,Resistor 1k 250mW through-hole,Multicomp,MF12 1K,Yageo,MFR-25FBF52-1K,RS Pro,7077666,,,,,1.00KXBK-ND,603MFR25FBF521K,7077666,38K5400,9342400
J2;,1,Lcr connector,JST,B14B-PHDSS (LF)(SN),,,,,,,,,455-1764-ND ,,918-2738,,
J4;J5;J6;J7;,4,BNC connector,TE,1-1337542-0,,,,,,,,,A97552-ND ,,512-1203,,
J8;,1,jumper connector,SamTec,SSW-103-01-G-S ,,,,,,,,,SAM1209-03-ND ,,765-5610,,
U1;U2;,2,SN74LS08N AND gate array,TI,SN74LS08N ,,,,,,,,,296-1633-5-ND,,,,
U3;,1,SN74HC14N Signal inverter (NOT gate) array,TI,SN74HC14N ,,,,,,,,,296-1577-5-ND ,,540-6885,,
,,,,,,,,,,,,,,,,,
Lcr 1,2,Female plug 2X14 (1 to Lcr one to Board),JST,PHDR-14VS ,,,,,,,,,455-1172-ND ,,917-4692,917-4692,
Cable,14,JUMPER SPHD-001T-P0.5 X2 10 ,JST,APAPA22K254 ,,,,,,,,,455-3357-ND ,,,,

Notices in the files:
boards/mosfet_circuit/mosfet_circuit.kicad_pcb:
CERN OHL-S V2.0
resources_for_zebra_fish/boards/lm2596_cc_vc/lm2596_cc_vc.kicad_pcb:
CERN OHL v1.2 20190208
